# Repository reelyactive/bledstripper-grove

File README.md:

bledstripper-grove
==================

Bluetooth Low Energy LED strip controller circuit board with standard Grove connectors.  Open hardware under the MIT License.

Overview
--------

The __bledstripper-grove__ combines a MDBT42Q Bluetooth Low Energy SoM and four Grove connectors that can be driven with high-amperage 5VDC power via a standard barrel connector.  It simplifies the wireless programming and control of up to four long strips of WS2813 LEDs (or equivalent).

LED Strips
----------

The __bledstripper-grove__ is designed to offer plug-and-play compatibility with [Seeed Studio's family of WS2813 LED strips](https://www.seeedstudio.com/Grove-WS2813-RGB-LED-Strip-Waterproof-30-LED-m-1m.html) which use standard Grove connectors.  The __bledstripper-grove__ is nonetheless compatible with the family of 5VDC addressable LEDs commonly referred to as NeoPixels, strips of which can alternatively be directly soldered to the through-hole connectors of J1-J4 of the board.

Schematic
---------

Key components
--------------

The __bledstripper-grove__ comprises the following three key components:
- [Raytac's MDBT42Q-512KV2 module](https://www.raytac.com/product/ins.php?index_id=31), which is based on the Nordic nRF52832 Bluetooth Low Energy IC, and which is [Espruino](https://www.espruino.com/MDBT42Q)-compatible.
- [TI's LP2985-33DBVR](https://www.ti.com/product/LP2985) 3.3V low-dropout voltage regulator to power the MDBT42Q
- [TI's TXU0104QPWRQ1](https://www.ti.com/product/TXU0104) four-channel voltage-level translator to convert the high-speed LED control signals from 3.3V to 5.0V

BOM selection was made to maximise [Shenzhen/Seeed OPL](https://www.seeedstudio.com/opl.html) (open parts library) components which include:

| Part number           | Shenzhen OPL SKU | Description   |
|:----------------------|:-----------------|---------------|
| MDBT42Q-512KV2        | 317030213        | E1 (SoC)      |
| LP2985-33DBVR         | 310030033        | U3 (LDO)      |
| 19-217-R6C-AL1M2VY-3T | 304090042        | D1 (Red)      |
| 19-217-BHC-ZL1M2RY-3T | 304090045        | D2 (Blue)     |
| 19-217-G7C-AN1P2-3T   | 304090043        | D3 (Green)    |
| 1125R-4P              | 320110034        | J1-J4 (Grove) |

MDBT42Q Pins
------------

| Function      | MDBT42Q Pin | nRF52832 Pin | Espruino Pin |
|:--------------|:------------|:-------------|:-------------|
| Red LED       | 16          | P0.3         | D3           |
| Blue LED      | 17          | P0.4         | D4           |
| Green LED     | 18          | P0.5         | D5           |
| Output Enable | 23          | P0.10        | D10          |
| LED data CH1  | 26          | P0.12        | D12          |
| LED data CH2  | 27          | P0.13        | D13          |
| LED data CH3  | 28          | P0.14        | D14          |
| LED data CH4  | 29          | P0.15        | D15          |

Enclosure
---------

The __bledstripper-grove__ is designed to fit the inexpensive [Hammond Manufacturing 1551K enclosure](https://www.hammfg.com/electronics/small-case/plastic/1551), which is available with or without flange, and in several colours.  Cutouts are required for the barrel connector and grove connectors.

Project History
---------------

The __bledstripper-grove__ is a collaboration between [reelyActive](https://www.reelyactive.com/) and [génielab.](https://genielab.co/), with the v0.1 layout completed by [TristanFranc](https://github.com/TristanFranc/).

License
-------

MIT License

Copyright (c) 2023 [reelyActive](https://www.reelyactive.com)

Permission is hereby granted, free of charge, to any person obtaining a copy of this software and associated documentation files (the "Software"), to deal in the Software without restriction, including without limitation the rights to use, copy, modify, merge, publish, distribute, sublicense, and/or sell copies of the Software, and to permit persons to whom the Software is furnished to do so, subject to the following conditions:

The above copyright notice and this permission notice shall be included in all copies or substantial portions of the Software.

THE SOFTWARE IS PROVIDED "AS IS", WITHOUT WARRANTY OF ANY KIND, EXPRESS OR 
IMPLIED, INCLUDING BUT NOT LIMITED TO THE WARRANTIES OF MERCHANTABILITY, 
FITNESS FOR A PARTICULAR PURPOSE AND NONINFRINGEMENT. IN NO EVENT SHALL THE 
AUTHORS OR COPYRIGHT HOLDERS BE LIABLE FOR ANY CLAIM, DAMAGES OR OTHER 
LIABILITY, WHETHER IN AN ACTION OF CONTRACT, TORT OR OTHERWISE, ARISING FROM, 
OUT OF OR IN CONNECTION WITH THE SOFTWARE OR THE USE OR OTHER DEALINGS IN 
THE SOFTWARE.

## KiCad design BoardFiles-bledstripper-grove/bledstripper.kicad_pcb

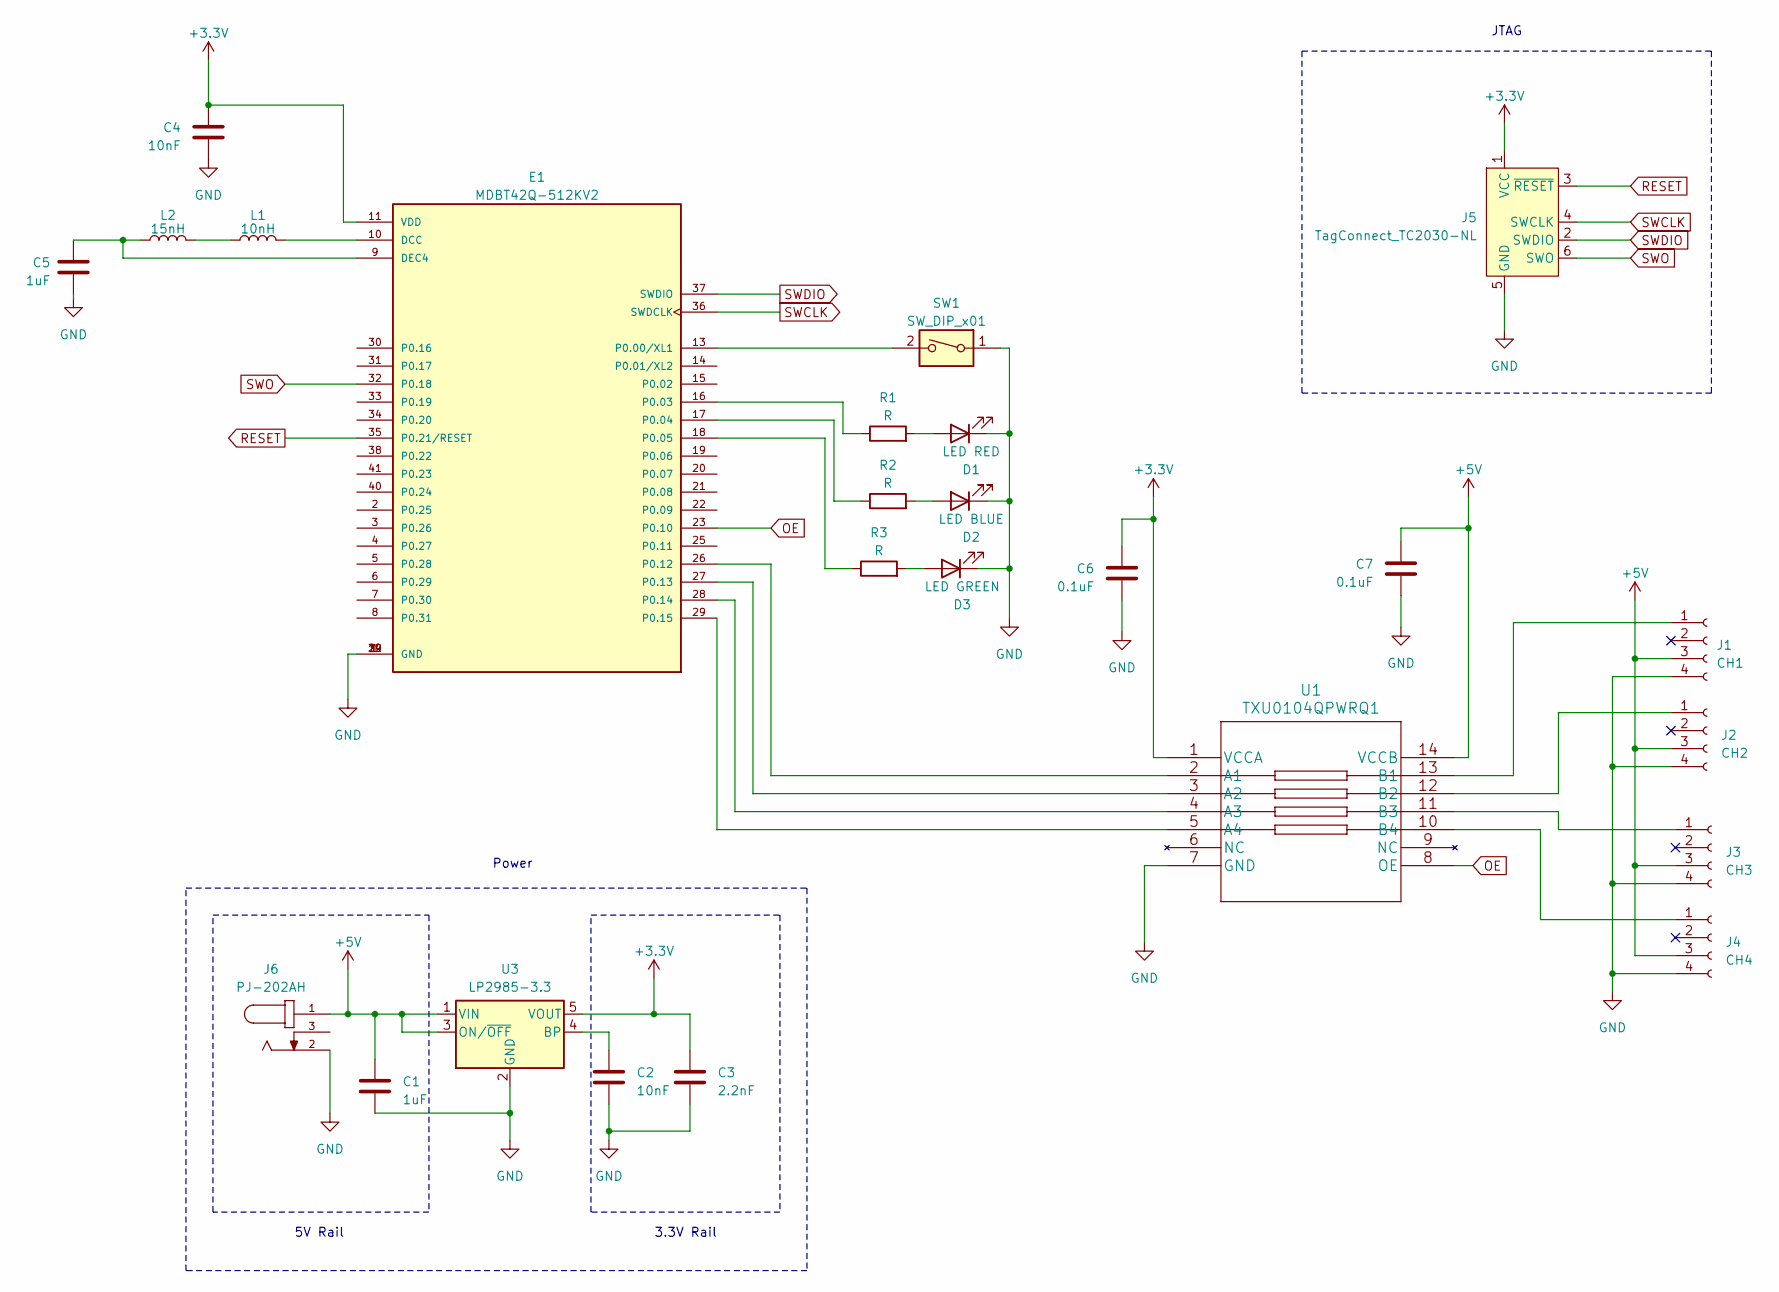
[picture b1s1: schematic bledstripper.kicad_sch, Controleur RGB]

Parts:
C1, C5: 1uF; C_0603_1608Metric_Pad1.08x0.95mm_HandSolder
C2, C4: 10nF; C_0603_1608Metric_Pad1.08x0.95mm_HandSolder
C3: 2.2nF; C_0603_1608Metric_Pad1.08x0.95mm_HandSolder
C6, C7: 0.1uF; C_0603_1608Metric_Pad1.08x0.95mm_HandSolder
D1: LED RED; LED_0603_1608Metric_Pad1.05x0.95mm_HandSolder
D2: LED BLUE; LED_0603_1608Metric_Pad1.05x0.95mm_HandSolder
D3: LED GREEN; LED_0603_1608Metric_Pad1.05x0.95mm_HandSolder
E1: MDBT42Q-512KV2; RAYTAC_MDBT42Q-512KV2; PARTREV J
J1: CH1; Grove Connector
J2: CH2; Grove Connector
J3: CH3; Grove Connector
J4: CH4; Grove Connector
J5: TagConnect_TC2030-NL; Tag-Connect_TC2030-IDC-NL_2x03_P1.27mm_Vertical
J6: PJ-202AH; CUI_PJ-202AH; PART_REV 1.02
L1: 10nH; L_0603_1608Metric_Pad1.05x0.95mm_HandSolder
L2: 15nH; L_0603_1608Metric_Pad1.05x0.95mm_HandSolder
R1, R2, R3: R; R_0603_1608Metric_Pad0.98x0.95mm_HandSolder
SW1: SW_DIP_x01; PinHeader_1x02_P2.54mm_Vertical
U1: TXU0104QPWRQ1
U3: LP2985-3.3; SOT-23-5

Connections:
+3.3V: C3.1, C4.1, C6.1, E1.11 (VDD), J5.1 (VCC), U1.1 (VCCA), U3.5 (VOUT)
+5V: C1.1, C7.1, J1.3, J2.3, J3.3, J4.3, J6.1, U1.14 (VCCB), U3.1 (VIN), U3.3 (ON/~OFF)
GND: C1.2, C2.2, C3.2, C4.2, C5.2, C6.2, C7.2, D1.1 (K), D2.1 (K), D3.1 (K), E1.1 (GND), E1.12 (GND), E1.24 (GND), E1.39 (GND), J1.4, J2.4, J3.4, J4.4, J5.5 (GND), J6.2, SW1.1, U1.7 (GND), U3.2 (GND)
unnamed: D1.2 (A), R1.2
unnamed: D2.2 (A), R2.2
unnamed: D3.2 (A), R3.2
unnamed: E1.10 (DCC), L1.1
unnamed: C5.1, E1.9 (DEC4), L2.2
unnamed: E1.13 (P0.00/XL1), SW1.2
unnamed: E1.16 (P0.03), R1.1
unnamed: E1.17 (P0.04), R2.1
unnamed: E1.18 (P0.05), R3.1
unnamed: E1.26 (P0.12), U1.2 (A1)
unnamed: E1.27 (P0.13), U1.3 (A2)
unnamed: E1.28 (P0.14), U1.4 (A3)
unnamed: E1.29 (P0.15), U1.5 (A4)
unnamed: J1.1, U1.13 (B1)
unnamed: J2.1, U1.12 (B2)
unnamed: J3.1, U1.11 (B3)
unnamed: J4.1, U1.10 (B4)
unnamed: L1.2, L2.1
unnamed: C2.1, U3.4 (BP)
OE: E1.23 (P0.10), U1.8 (OE)
RESET: E1.35 (P0.21/RESET), J5.3 (~RESET)
SWCLK: E1.36 (SWDCLK), J5.4 (SWCLK)
SWDIO: E1.37 (SWDIO), J5.2 (SWDIO)
SWO: E1.32 (P0.18), J5.6 (SWO)

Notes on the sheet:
3.3V Rail
5V Rail
Power
JTAG

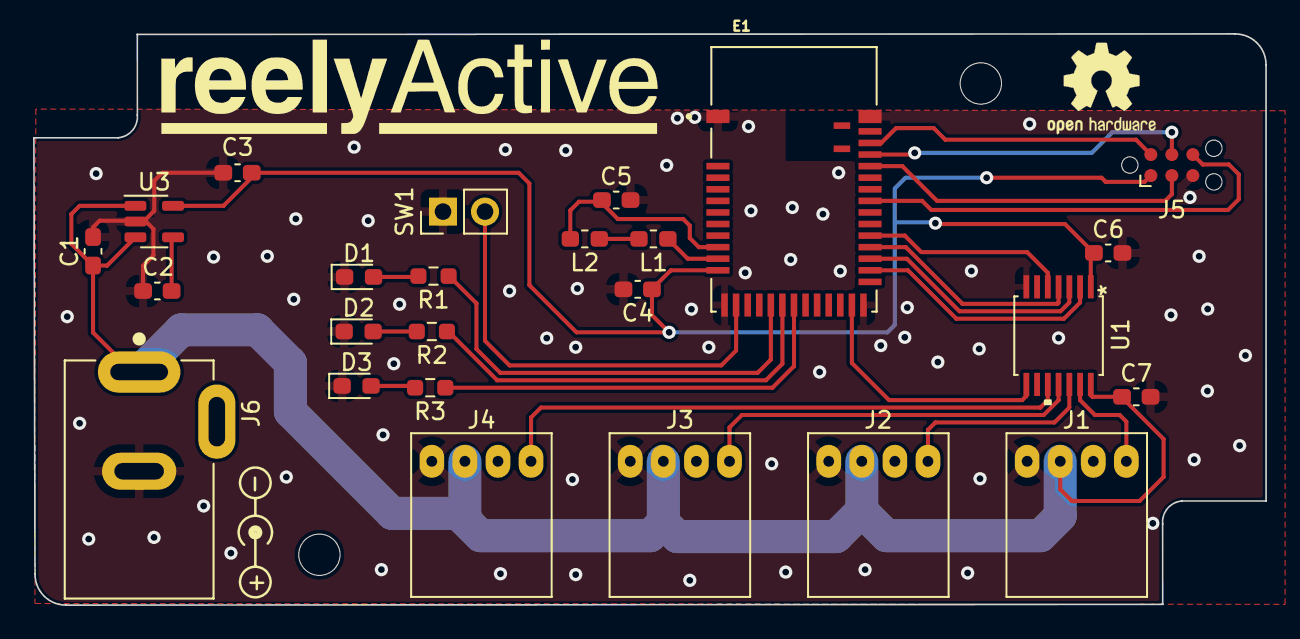
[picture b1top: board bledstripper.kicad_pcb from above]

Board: 2 copper layers, 74.5 x 34.5 mm, 25 parts (0 on the bottom side), 27 nets.

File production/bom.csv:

Designator,Footprint,Quantity,Value,LCSC Part #
"C1, C5",0603,2,1uF,
"C2, C4",0603,2,10nF,
C3,0603,1,2.2nF,
"C6, C7",0603,2,0.1uF,
D1,0603,1,LED RED,
D2,0603,1,LED BLUE,
D3,0603,1,LED GREEN,
E1,RAYTAC_MDBT42Q-512KV2,1,MDBT42Q-512KV2,
J1,Grove Connector,1,CH1,
J2,Grove Connector,1,CH2,
J3,Grove Connector,1,CH3,
J4,Grove Connector,1,CH4,
J5,Tag-Connect_TC2030-IDC-NL_2x03_P1.27mm_Vertical,1,TagConnect_TC2030-NL,
J6,CUI_PJ-202AH,1,PJ-202AH,
L1,0603,1,10nH,
L2,0603,1,15nH,
"R1, R2, R3",0603,3,R,
SW1,PinHeader_1x02_P2.54mm_Vertical,1,SW_DIP_x01,
U1,TXU0104QPWRQ1,1,TXU0104QPWRQ1,
U3,SOT-23-5,1,LP2985-3.3,

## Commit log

2023-03-18 Added license and basic description to README.
2023-03-20 Add files via upload
    Initial upload
2023-08-31 Added MDBT42Q pins
2023-09-15 Added schematic
2023-09-15 Added render
2023-09-15 Added Overview, LED Strips & Schematic sections
2023-09-15 Added Key Components and Enclosure sections
2023-09-15 Added Project History section with contributions
